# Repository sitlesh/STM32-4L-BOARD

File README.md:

# STM32 Custom Development Board (v1.0)

A highly compact, professionally optimized 4-layer custom development board for the STM32 Microcontroller, designed using KiCad 10.0. The layout utilizes a dedicated 4-layer stackup to achieve superior signal integrity, low-noise power distribution, and a minimal form factor.

---

## 🎛️ Layer Stackup
* **Top Layer (F.Cu):** High-speed signal routing and component placement.
* **Internal Layer 1 (In1.Cu):** Dedicated Ground Plane (GND) for EMI shielding.
* **Internal Layer 2 (In2.Cu):** Dedicated Power Plane (3.3V) for stable power distribution.
* **Bottom Layer (B.Cu):** Auxiliary signal routing and ground pour.

---

## 🚀 Features
* **Microcontroller:** STM32 (LQFP-48 package).
* **Power & Connectivity:** USB Type-C interface for power and data.
* **Stackup Optimization:** Dedicated internal power/ground planes to minimize loop inductance.
* **Clock System:** External crystal oscillator circuit.
* **User Interface:** On-board programmable push-button and status LED.

---

## 🛠️ Tech Stack & Software
* **EDA Tool:** KiCad v8.0
* **Manufacturing Standards:** DRC Verified (0 Errors, 0 Unconnected Items), Gerber X2 compliant.

---

## 📦 Project Structure & Quick Links

* 📝 **Schematic File:** [`STM32-4L-MCU-BOARD.kicad_sch`](STM32-4L-MCU-BOARD.kicad_sch) — Complete 4-layer circuit diagram.
* 🎛️ **PCB Layout File:** [`STM32-4L-MCU-BOARD.kicad_pcb`](STM32-4L-MCU-BOARD.kicad_pcb) — 4-Layer board routing and stackup definition.
* ⚙️ **Project File:** [`STM32-4L-MCU-BOARD.kicad_pro`](STM32-4L-MCU-BOARD.kicad_pro) — KiCad project configuration file.
* 📦 **Production Ready Gerbers:** [`Gerbers.zip`](Gerbers.zip) — Contains all Gerber X2 and drill files, ready to upload to JLCPCB, PCBWay, or local fabs.
* 📸 **Design Images:** [`Images/`](Images/) — Folder containing board screenshots and 3D renders.
---
---

## 📸 Design Preview

### 1. 3D Render View

### 2. PCB Layout Design

### 3. Gerber Viewer View

---

## 🔍 High-Resolution Links

* 🌐 **Full 3D Render:** [Click here to view 3D Render](Images/3D%20View.png)
* 🗺️ **Full PCB Layout:** [Click here to view Layout Screenshot](Images/Layout.png)
* 🔬 **Full Gerber View:** [Click here to view Gerber Screenshot](Images/Gerber%20view.png)

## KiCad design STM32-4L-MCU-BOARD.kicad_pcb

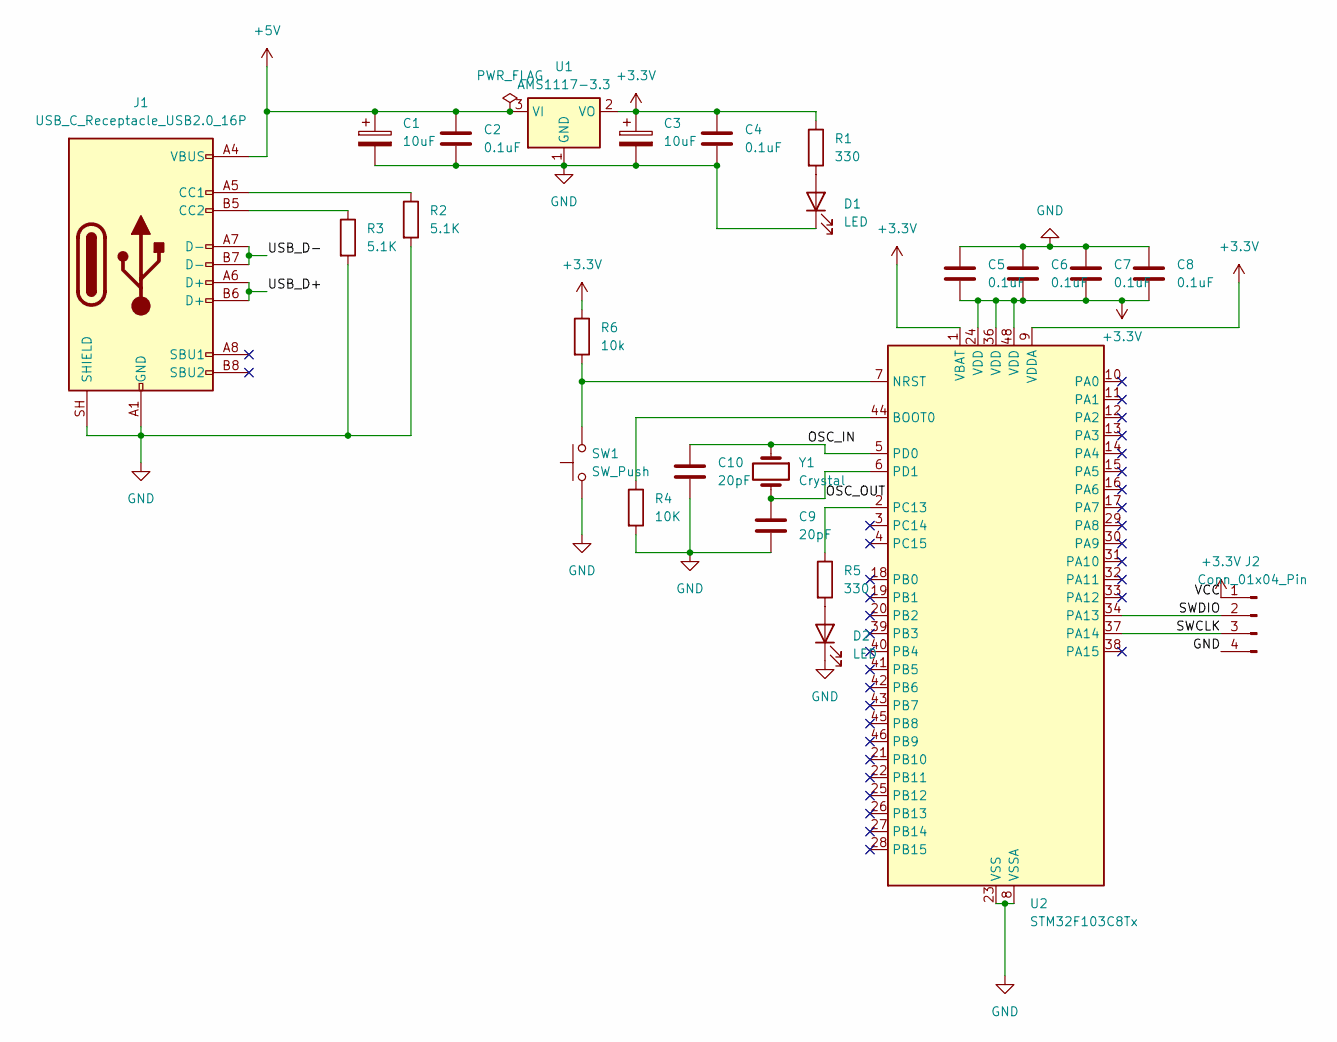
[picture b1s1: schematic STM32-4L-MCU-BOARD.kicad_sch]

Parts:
C1, C3: 10uF; C_1206_3216Metric
C2, C4, C5, C6, C7, C8: 0.1uF; C_0805_2012Metric
C9, C10: 20pF; C_0805_2012Metric
D1, D2: LED; LED_0805_2012Metric
J1: USB_C_Receptacle_USB2.0_16P; USB_C_Receptacle_HRO_TYPE-C-31-M-12
J2: Conn_01x04_Pin; PinHeader_1x04_P2.54mm_Vertical_SMD_Pin1Left
R1: 330; LED_0805_2012Metric
R2, R3: 5.1K; R_0805_2012Metric
R4: 10K; R_0805_2012Metric
R5: 330; R_0805_2012Metric
R6: 10k; R_0805_2012Metric
SW1: SW_Push; SW_Push_1P1T_NO_CK_KSC6xxG
U1: AMS1117-3.3; SOT-223-3_TabPin2
U2: STM32F103C8Tx; LQFP-48_7x7mm_P0.5mm
Y1: Crystal; Crystal_SMD_5032-2Pin_5.0x3.2mm

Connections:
+3.3V: C3.1, C4.1, C5.2, C6.2, C7.2, C8.2, J2.1, R1.1, R6.1, U1.2 (VO), U2.1 (VBAT), U2.9 (VDDA), U2.24 (VDD), U2.36 (VDD), U2.48 (VDD)
+5V: C1.1, C2.1, J1.A4 (VBUS), J1.A9 (VBUS), J1.B4 (VBUS), J1.B9 (VBUS), U1.3 (VI)
/OSC_IN: C10.1, U2.5 (PD0), Y1.1
/OSC_OUT: C9.1, U2.6 (PD1), Y1.2
/SWCLK: J2.3, U2.37 (PA14)
/SWDIO: J2.2, U2.34 (PA13)
/USB_D+: J1.A6 (D+), J1.B6 (D+)
/USB_D-: J1.A7 (D-), J1.B7 (D-)
GND: C1.2, C2.2, C3.2, C4.2, C5.1, C6.1, C7.1, C8.1, C9.2, C10.2, D1.1 (K), D2.1 (K), J1.A1 (GND), J1.A12 (GND), J1.B1 (GND), J1.B12 (GND), J1.SH (SHIELD), J2.4, R2.2, R3.2, R4.2, SW1.1, U1.1 (GND), U2.8 (VSSA), U2.23 (VSS), U2.35 (VSS), U2.47 (VSS)
unnamed: D1.2 (A), R1.2
unnamed: D2.2 (A), R5.2
unnamed: J1.A5 (CC1), R2.1
unnamed: J1.B5 (CC2), R3.1
unnamed: R4.1, U2.44 (BOOT0)
unnamed: R6.2, SW1.2, U2.7 (NRST)
unnamed: R5.1, U2.2 (PC13)

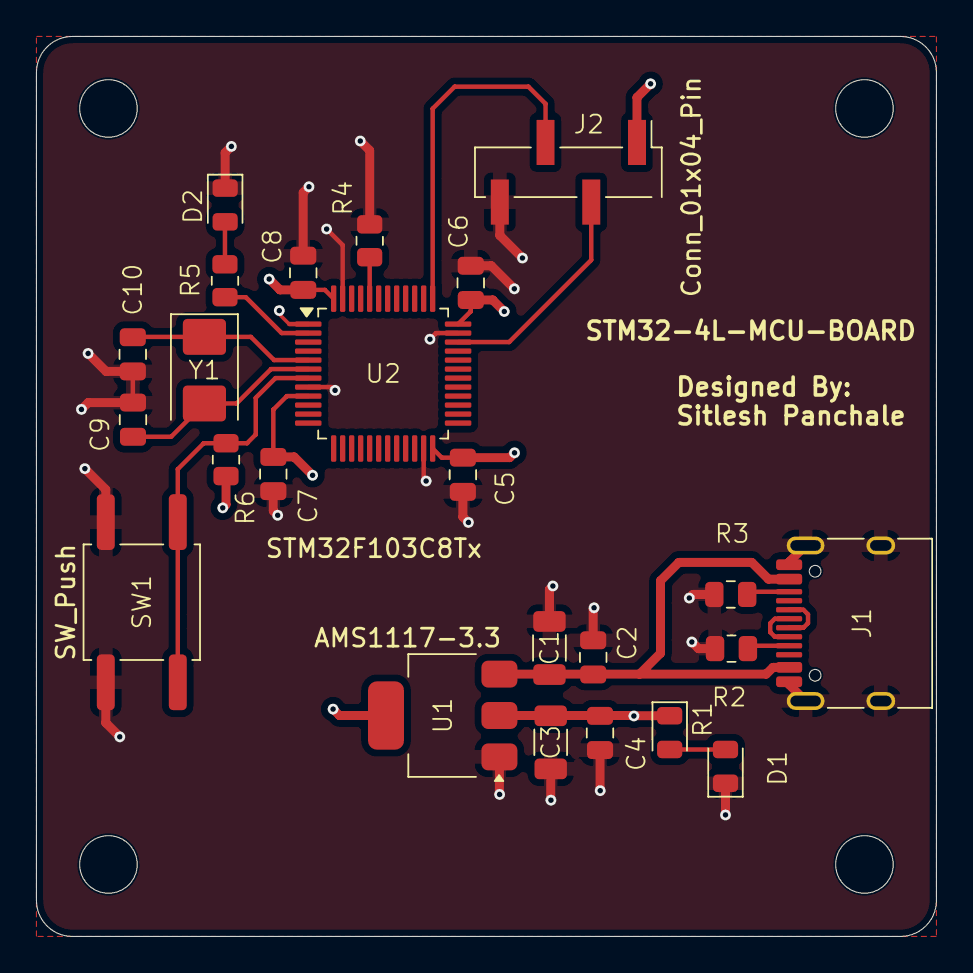
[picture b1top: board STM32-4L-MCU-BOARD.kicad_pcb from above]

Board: 4 copper layers, 50.0 x 50.0 mm, 24 parts (0 on the bottom side), 16 nets.

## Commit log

2026-05-29 Rename Screenshot (41).png to Layout.png
2026-05-29 Rename STM32-4L-MCU-BOARD.png to 3D View.png
2026-05-29 Rename Screenshot (45).png to Gerber view.png
